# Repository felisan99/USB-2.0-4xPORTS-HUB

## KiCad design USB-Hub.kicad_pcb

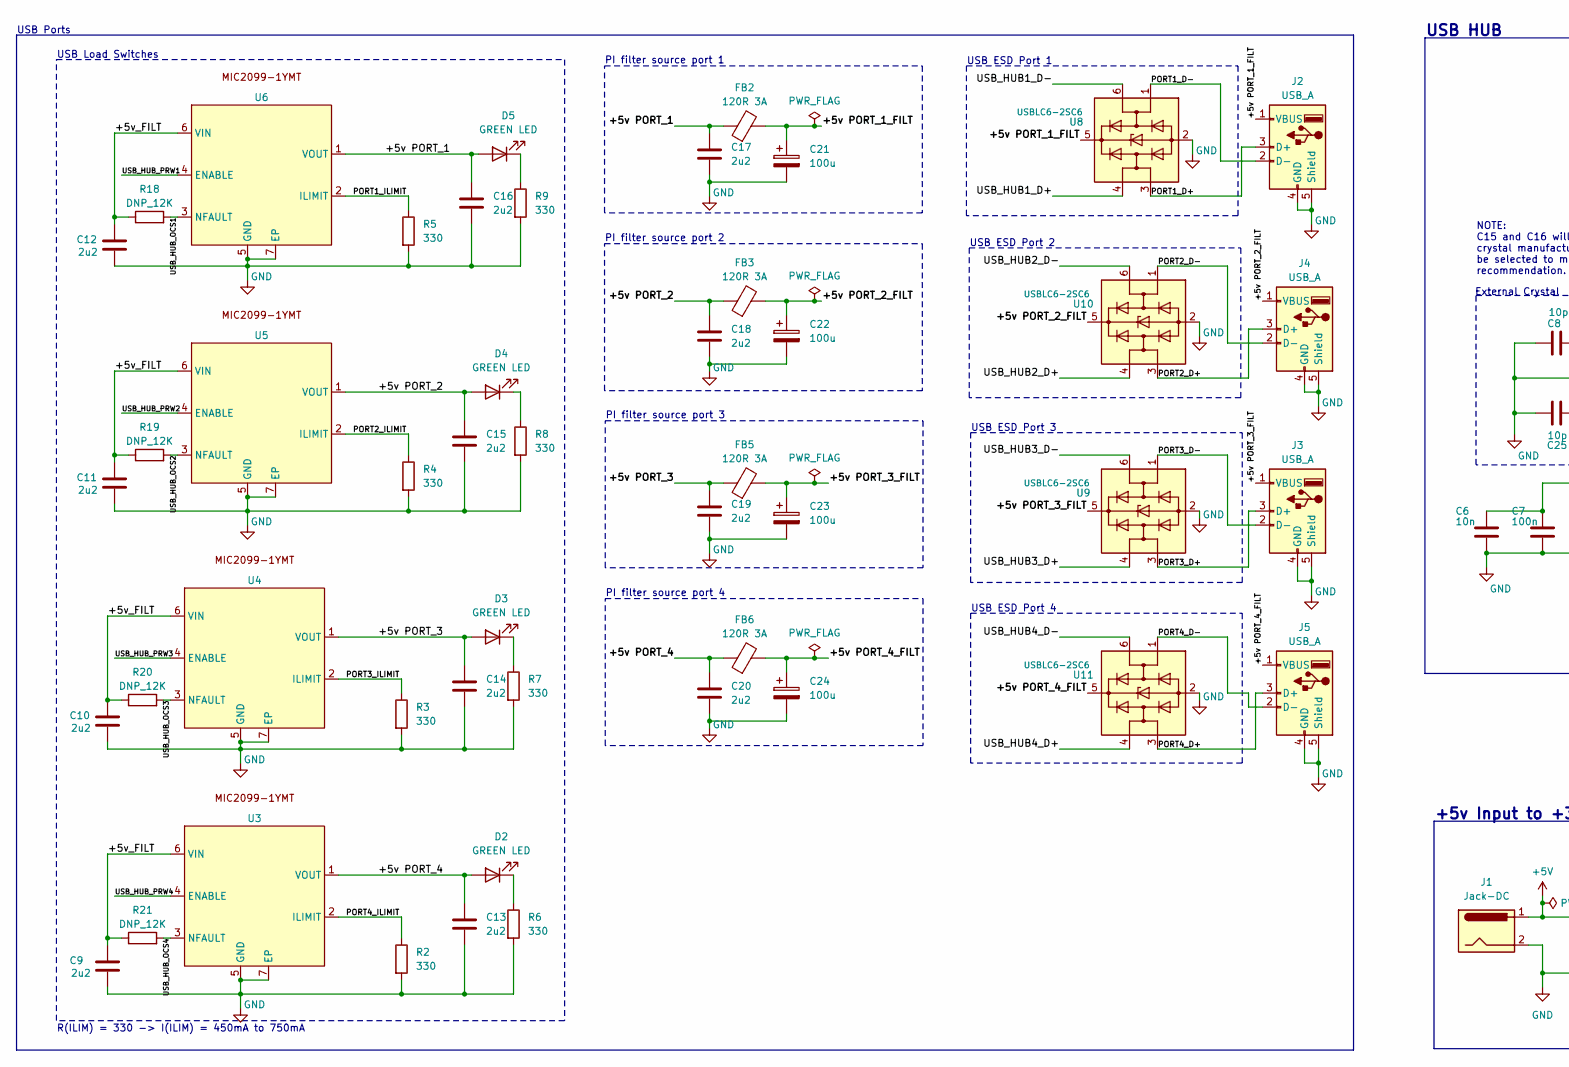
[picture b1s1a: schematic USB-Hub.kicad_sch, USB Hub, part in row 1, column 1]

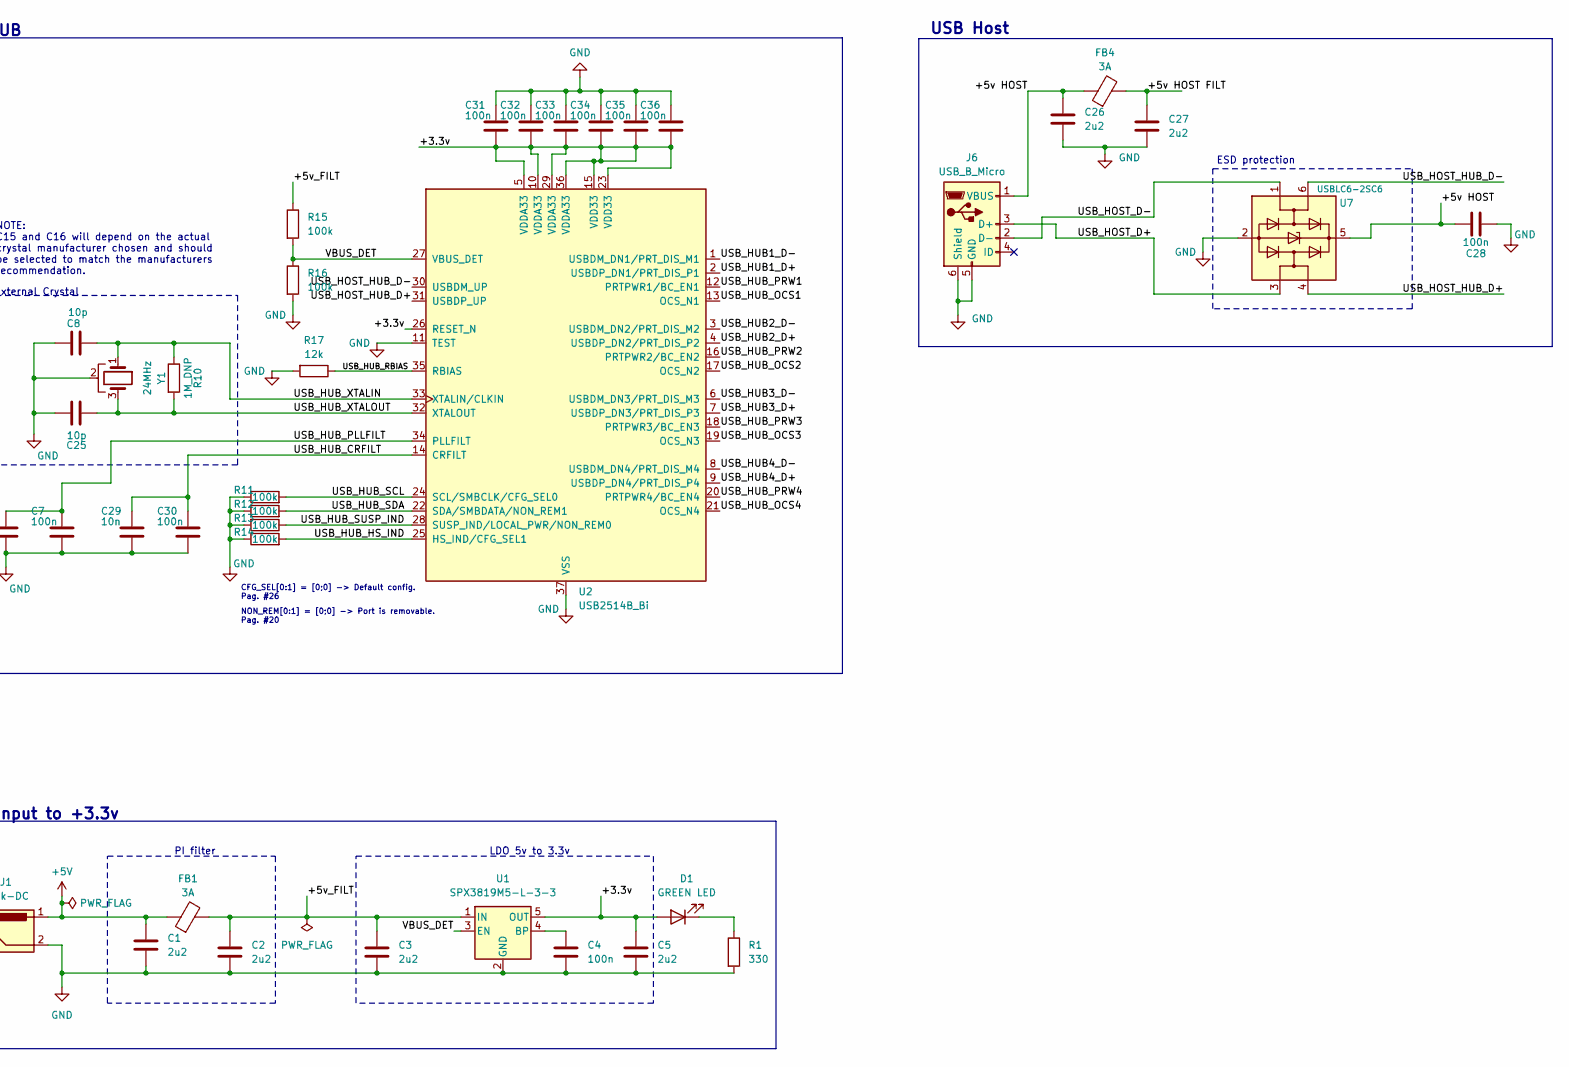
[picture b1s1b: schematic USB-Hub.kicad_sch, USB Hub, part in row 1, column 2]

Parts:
C1, C2, C3, C5, C9, C10, C11, C12, C13, C14, C15, C16, C17, C18, C19, C20, C26, C27: 2u2; C_0805_2012Metric
C4, C7, C28, C30: 100n; C_0805_2012Metric
C6, C29: 10n; C_0603_1608Metric
C8, C25: 10p; C_0603_1608Metric
C21, C22, C23, C24: 100u; CP_Elec_6.3x3.9
C31, C32, C33, C34, C35, C36: 100n; C_0603_1608Metric
D1, D2, D3, D4, D5: GREEN LED; LED_0805_2012Metric
FB1, FB4: 3A; L_0201_0603Metric
FB2, FB3, FB5, FB6: 120R 3A; L_0201_0603Metric
J1: Jack-DC; BarrelJack_Horizontal
J2, J3, J4, J5: USB_A; USB_A_TE_292303-7_Horizontal
J6: USB_B_Micro; USB_Micro-B_Molex_47346-0001
R1, R2, R3, R4, R5, R6, R7, R8, R9: 330; R_0201_0603Metric
R10: 1M_DNP; R_0805_2012Metric
R11, R12, R13, R14, R15, R16: 100k; R_0805_2012Metric
R17: 12k; R_0201_0603Metric
R18, R19, R20, R21: DNP_12K; R_0201_0603Metric
U1: SPX3819M5-L-3-3; SOT-23-5
U2: USB2514B_Bi; QFN-36-1EP_6x6mm_P0.5mm_EP3.7x3.7mm
U3, U4, U5, U6: MIC2099-1YMT
U7, U8, U9, U10, U11: USBLC6-2SC6; SOT-23-6
Y1: 24MHz; Resonator_SMD-3Pin_7.2x3.0mm

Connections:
+5V: C1.1, FB1.1, J1.1
/+3.3v: C5.1, C31.2, C32.2, C33.2, C34.2, C35.2, C36.2, D1.2 (A), U1.5 (OUT), U2.5 (VDDA33), U2.10 (VDDA33), U2.15 (VDD33), U2.23 (VDD33), U2.26 (RESET_N), U2.29 (VDDA33), U2.36 (VDDA33)
/+5v HOST: C26.1, C28.1, FB4.1, J6.1 (VBUS), U7.5 (VBUS)
/+5v HOST FILT: C27.1, FB4.2
/+5v PORT_1: C16.1, C17.1, D5.2 (A), FB2.1, U6.1 (VOUT)
/+5v PORT_1_FILT: C21.1, FB2.2, J2.1 (VBUS), U8.5 (VBUS)
/+5v PORT_2: C15.1, C18.1, D4.2 (A), FB3.1, U5.1 (VOUT)
/+5v PORT_2_FILT: C22.1, FB3.2, J4.1 (VBUS), U10.5 (VBUS)
/+5v PORT_3: C14.1, C19.1, D3.2 (A), FB5.1, U4.1 (VOUT)
/+5v PORT_3_FILT: C23.1, FB5.2, J3.1 (VBUS), U9.5 (VBUS)
/+5v PORT_4: C13.1, C20.1, D2.2 (A), FB6.1, U3.1 (VOUT)
/+5v PORT_4_FILT: C24.1, FB6.2, J5.1 (VBUS), U11.5 (VBUS)
/+5v_FILT: C2.1, C3.1, C9.1, C10.1, C11.1, C12.1, FB1.2, R15.1, R18.1, R19.1, R20.1, R21.1, U1.1 (IN), U3.6 (VIN), U4.6 (VIN), U5.6 (VIN), U6.6 (VIN)
/PORT1_D+: J2.3 (D+), U8.3 (I/O2)
/PORT1_D-: J2.2 (D-), U8.1 (I/O1)
/PORT1_ILIMIT: R5.1, U6.2 (ILIMIT)
/PORT2_D+: J4.3 (D+), U10.3 (I/O2)
/PORT2_D-: J4.2 (D-), U10.1 (I/O1)
/PORT2_ILIMIT: R4.1, U5.2 (ILIMIT)
/PORT3_D+: J3.3 (D+), U9.3 (I/O2)
/PORT3_D-: J3.2 (D-), U9.1 (I/O1)
/PORT3_ILIMIT: R3.1, U4.2 (ILIMIT)
/PORT4_D+: J5.3 (D+), U11.3 (I/O2)
/PORT4_D-: J5.2 (D-), U11.1 (I/O1)
/PORT4_ILIMIT: R2.1, U3.2 (ILIMIT)
/USB_HOST_D+: J6.3 (D+), U7.3 (I/O2)
/USB_HOST_D-: J6.2 (D-), U7.1 (I/O1)
/USB_HOST_HUB_D+: U2.31 (USBDP_UP), U7.4 (I/O2)
/USB_HOST_HUB_D-: U2.30 (USBDM_UP), U7.6 (I/O1)
/USB_HUB1_D+: U2.2 (USBDP_DN1/PRT_DIS_P1), U8.4 (I/O2)
/USB_HUB1_D-: U2.1 (USBDM_DN1/PRT_DIS_M1), U8.6 (I/O1)
/USB_HUB2_D+: U2.4 (USBDP_DN2/PRT_DIS_P2), U10.4 (I/O2)
/USB_HUB2_D-: U2.3 (USBDM_DN2/PRT_DIS_M2), U10.6 (I/O1)
/USB_HUB3_D+: U2.7 (USBDP_DN3/PRT_DIS_P3), U9.4 (I/O2)
/USB_HUB3_D-: U2.6 (USBDM_DN3/PRT_DIS_M3), U9.6 (I/O1)
/USB_HUB4_D+: U2.9 (USBDP_DN4/PRT_DIS_P4), U11.4 (I/O2)
/USB_HUB4_D-: U2.8 (USBDM_DN4/PRT_DIS_M4), U11.6 (I/O1)
/USB_HUB_CRFILT: C29.1, C30.1, U2.14 (CRFILT)
/USB_HUB_HS_IND: R14.2, U2.25 (HS_IND/CFG_SEL1)
/USB_HUB_OCS1: R18.2, U2.13 (OCS_N1), U6.3 (NFAULT)
/USB_HUB_OCS2: R19.2, U2.17 (OCS_N2), U5.3 (NFAULT)
/USB_HUB_OCS3: R20.2, U2.19 (OCS_N3), U4.3 (NFAULT)
/USB_HUB_OCS4: R21.2, U2.21 (OCS_N4), U3.3 (NFAULT)
/USB_HUB_PLLFILT: C6.1, C7.1, U2.34 (PLLFILT)
/USB_HUB_PRW1: U2.12 (PRTPWR1/BC_EN1), U6.4 (ENABLE)
/USB_HUB_PRW2: U2.16 (PRTPWR2/BC_EN2), U5.4 (ENABLE)
/USB_HUB_PRW3: U2.18 (PRTPWR3/BC_EN3), U4.4 (ENABLE)
/USB_HUB_PRW4: U2.20 (PRTPWR4/BC_EN4), U3.4 (ENABLE)
/USB_HUB_RBIAS: R17.1, U2.35 (RBIAS)
/USB_HUB_SCL: R11.2, U2.24 (SCL/SMBCLK/CFG_SEL0)
/USB_HUB_SDA: R12.2, U2.22 (SDA/SMBDATA/NON_REM1)
/USB_HUB_SUSP_IND: R13.1, U2.28 (SUSP_IND/LOCAL_PWR/NON_REM0)
/USB_HUB_XTALIN: C8.1, R10.1, U2.33 (XTALIN/CLKIN), Y1.1
/USB_HUB_XTALOUT: C25.2, R10.2, U2.32 (XTALOUT), Y1.3
/VBUS_DET: R15.2, R16.1, U1.3 (EN), U2.27 (VBUS_DET)
GND: C1.2, C2.2, C3.2, C4.2, C5.2, C6.2, C7.2, C8.2, C9.2, C10.2, C11.2, C12.2, C13.2, C14.2, C15.2, C16.2, C17.2, C18.2, C19.2, C20.2, C21.2, C22.2, C23.2, C24.2, C25.1, C26.2, C27.2, C28.2, C29.2, C30.2, C31.1, C32.1, C33.1, C34.1, C35.1, C36.1, J1.2, J2.4 (GND), J2.5 (Shield), J3.4 (GND), J3.5 (Shield), J4.4 (GND), J4.5 (Shield), J5.4 (GND), J5.5 (Shield), J6.5 (GND), J6.6 (Shield), R1.2, R2.2, R3.2, R4.2, R5.2, R6.2, R7.2, R8.2, R9.2, R11.1, R12.1, R13.2, R14.1, R16.2, R17.2, U1.2 (GND), U2.11 (TEST), U2.37 (VSS), U3.5 (GND), U3.7 (EP), U4.5 (GND), U4.7 (EP), U5.5 (GND), U5.7 (EP), U6.5 (GND), U6.7 (EP), U7.2 (GND), U8.2 (GND), U9.2 (GND), U10.2 (GND), U11.2 (GND), Y1.2
unnamed: D1.1 (K), R1.1
unnamed: D2.1 (K), R6.1
unnamed: D3.1 (K), R7.1
unnamed: D4.1 (K), R8.1
unnamed: D5.1 (K), R9.1
unnamed: C4.1, U1.4 (BP)

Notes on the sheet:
PI filter source port 4
+5v Input to +3.3v
R(ILIM) = 330 -> I(ILIM) = 450mA to 750mA
USB Host
USB ESD Port 2
USB HUB
PI filter
LDO 5v to 3.3v
NOTE: C15 and C16 will depend on the actual crystal manufacturer chosen and should be selected to match the manufacturers recommendation.
USB Load Switches
USB ESD Port 1
USB Ports
USB ESD Port 4
PI filter source port 3
NON_REM[0:1] = [0;0] -> Port is removable. Pag. #20
ESD protection
External Crystal
USB ESD Port 3
PI filter source port 2
CFG_SEL[0:1] = [0;0] -> Default config. Pag. #26
PI filter source port 1

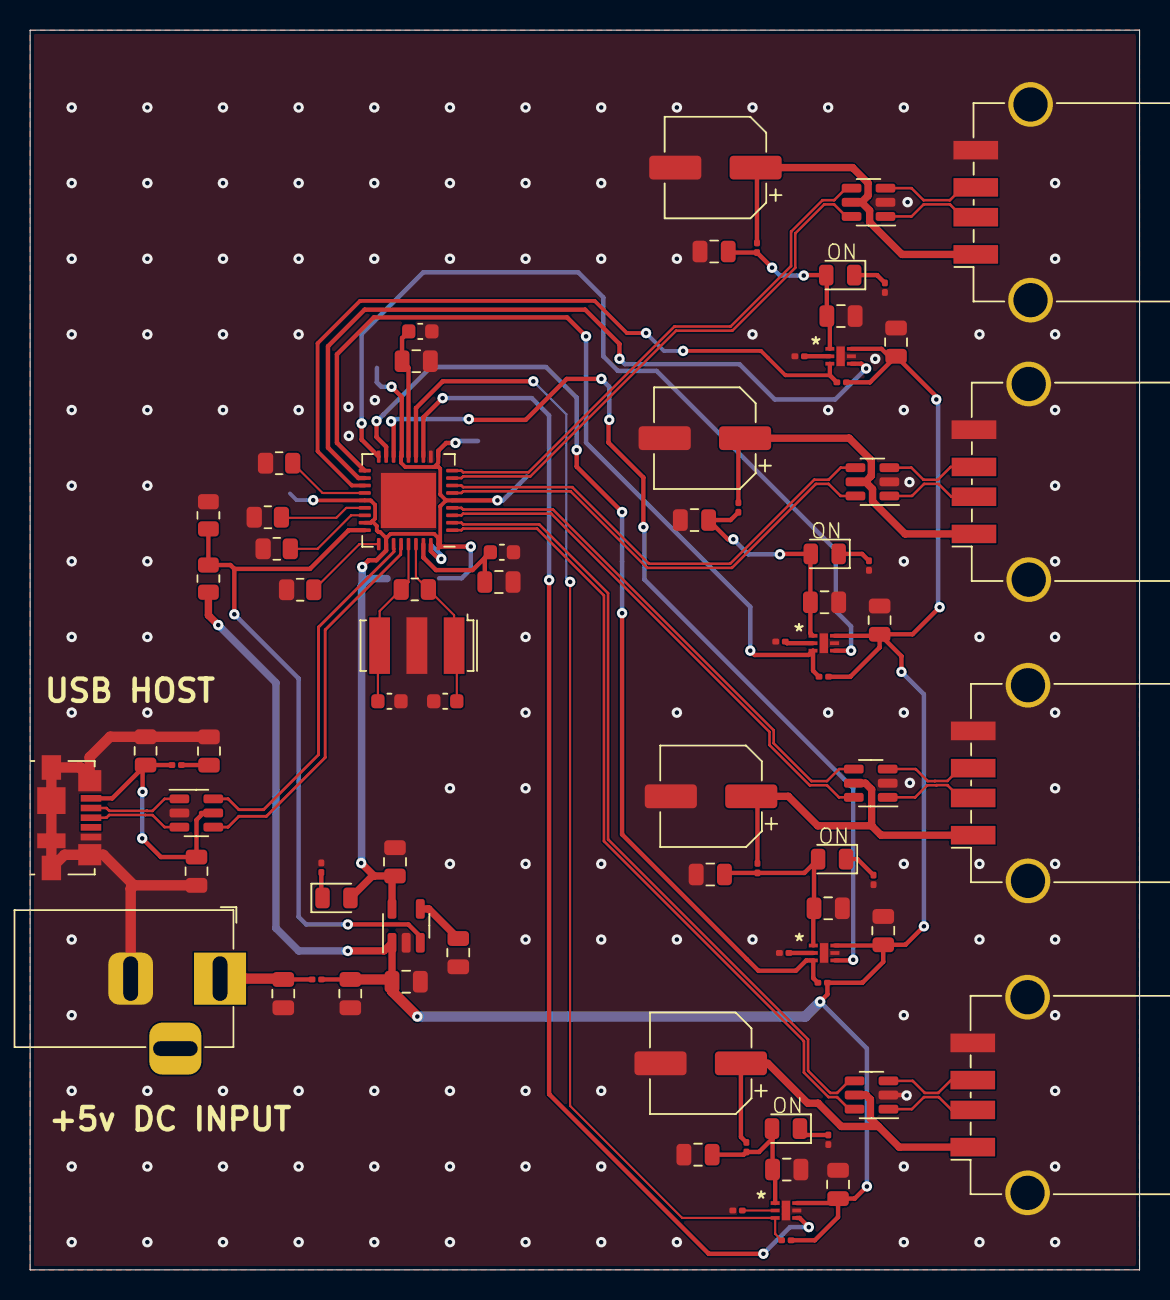
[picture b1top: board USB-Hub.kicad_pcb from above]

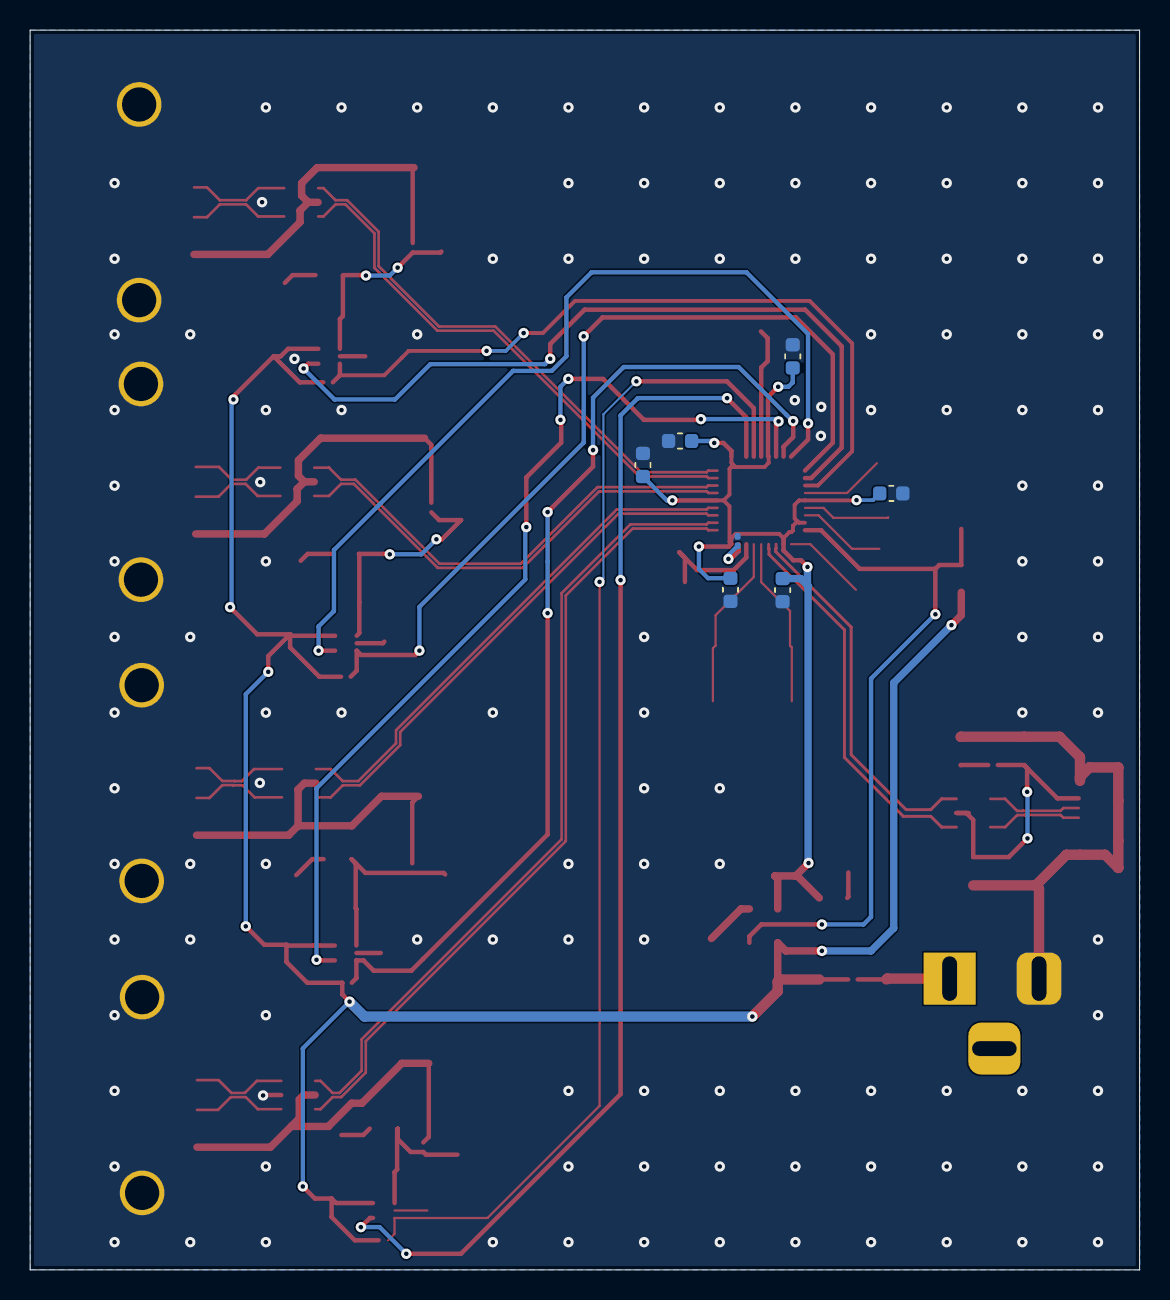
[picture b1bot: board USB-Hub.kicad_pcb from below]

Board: 4 copper layers, 74.5 x 83.2 mm, 86 parts (7 on the bottom side), 62 nets.

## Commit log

2025-02-19 upload
